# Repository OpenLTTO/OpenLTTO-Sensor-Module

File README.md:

# OpenLTTO
The OpenLTTO Project is an attempt to recreate the Lazer Tag Team Ops protocol, and game system, in a completely open-source solution. Eventually our intent, is to expand on the LTTO system, adding new functionality, and features, while maintaining backwards compatibility with this classic Lazer Tag gear.

> This Project wouldn't be possible without all the hard work of Richie Mickan https://github.com/rmick
> His work on recreating the LTTO Protocol, and the development of the Combobulator app are core to the firmware and capabilities of this project.

> Additionally this is built on top of the excellent product developed and released by Hasbro/Tiger Electronics. And the work done by Tag Ferret to release the technical specs, and unlock much of the magic of the protocol, and the inner workings.

We intend to do this via a collection of open-source hardware components that can act as building blocks, to build anything you might require for a Lazer Tag game (Taggers, Hosting Pods, Zone controllers, utilities, etc). And an opensource firmware to operate it all. 

Shield: [![CC BY-NC-SA 4.0][cc-by-nc-sa-shield]][cc-by-nc-sa]

This work is licensed under a
[Creative Commons Attribution-NonCommercial-ShareAlike 4.0 International License][cc-by-nc-sa].

[![CC BY-NC-SA 4.0][cc-by-nc-sa-image]][cc-by-nc-sa]

[cc-by-nc-sa]: http://creativecommons.org/licenses/by-nc-sa/4.0/
[cc-by-nc-sa-image]: https://licensebuttons.net/l/by-nc-sa/4.0/88x31.png
[cc-by-nc-sa-shield]: https://img.shields.io/badge/License-CC%20BY--NC--SA%204.0-lightgrey.svg

# OpenLTTO Sensor Module
The OpenLTTO Sensor Module is designed to act as either a sensor dome on a Tagger, or a sensor dome on a "Hosting Station" (such as for use with Combobulator), or within a utility component (Zones, Grenades, or any other component you can think of that needs to use 360 degree IR).

It is designed to be paired with a 50mm clear dome, and encased in a 3D Printed "Sensor Module" chassis which can then be embedded in other projects such as Taggers etc.

The module includes 5 Pin IR IN and IR OUT ports, and 4x pairs of IR Transmitter and IR Receiver. The transmitters are more wide angle (TSAL6400) compared to the barrel module, and with this arrangement should provide effective 360 degree coverage. The circuit includes an optimized 1A LED Driver for each IR LED, ensuring full current output per LED. The Module supports both outdoor (high power, 1A), and indoor (low power) modes, controlled from the motherboard. And includes a 2x power ballasts (capacitor, and inrush arrester pair) to prevent ripples, and ensure smooth operation.

## OpenLTTO Sensor Module Top Side

## OpenLTTO Sensor Module Bottom Side

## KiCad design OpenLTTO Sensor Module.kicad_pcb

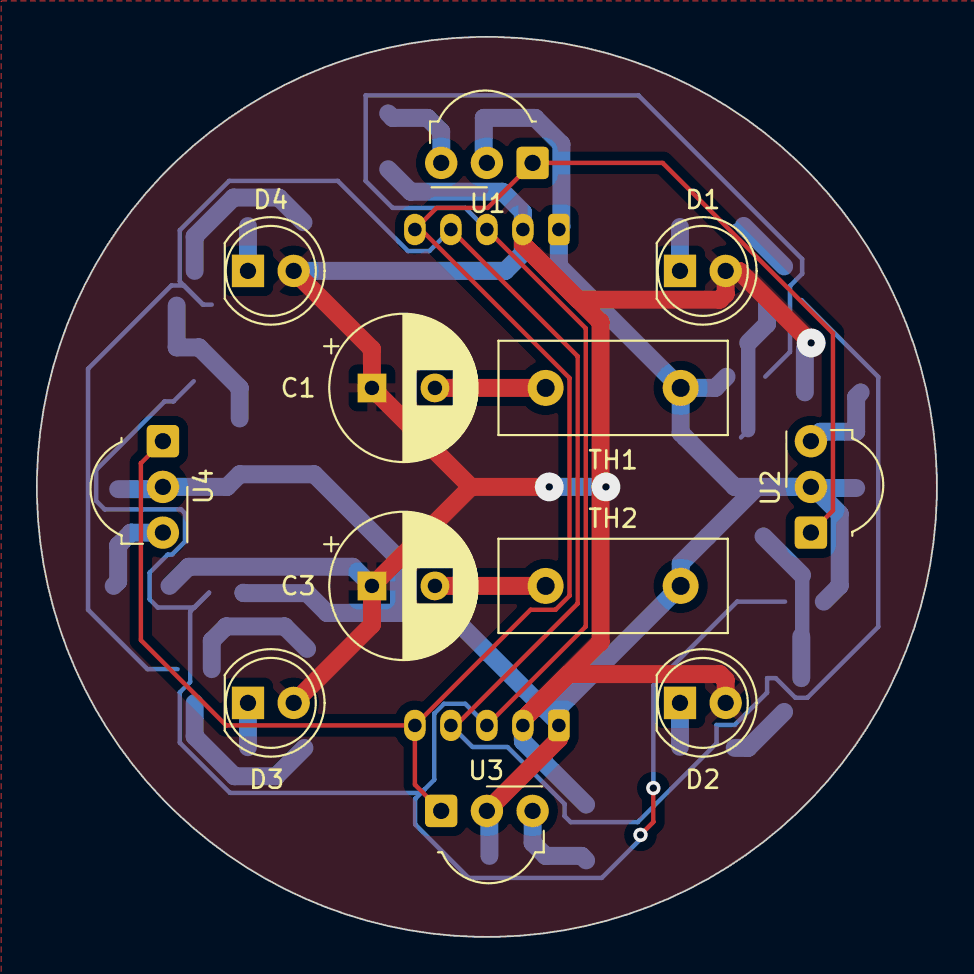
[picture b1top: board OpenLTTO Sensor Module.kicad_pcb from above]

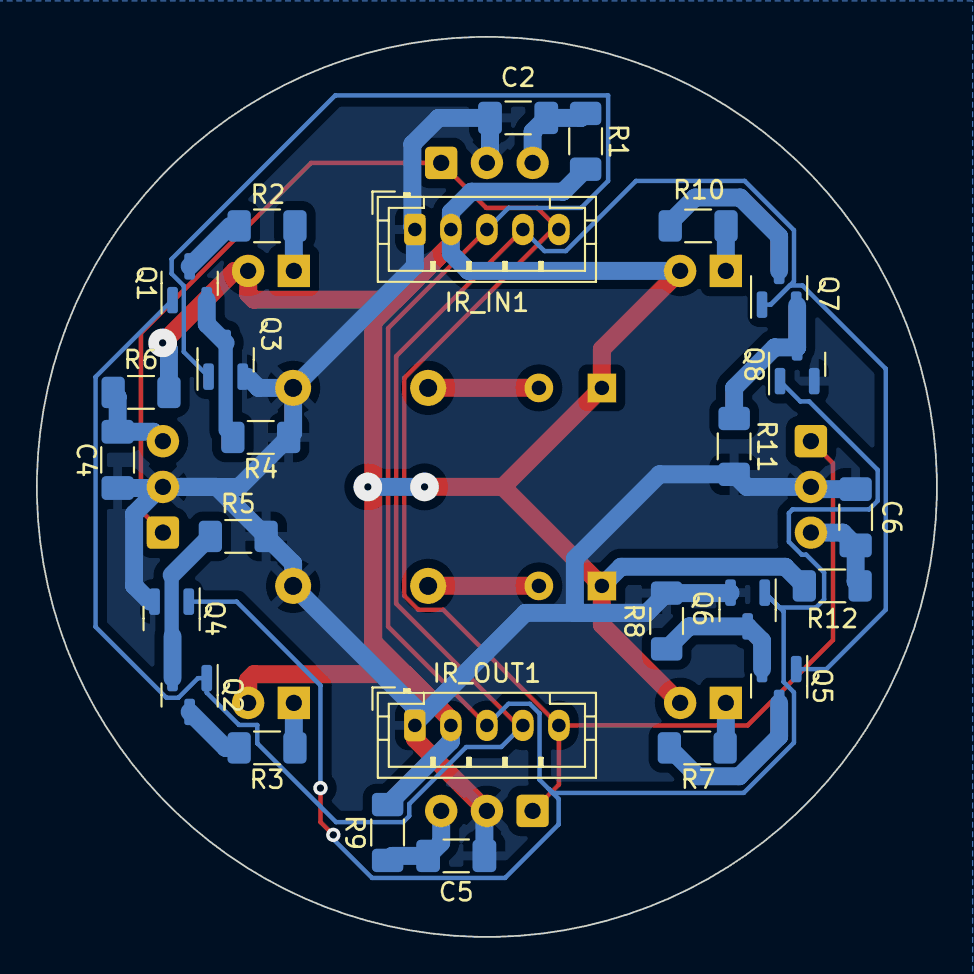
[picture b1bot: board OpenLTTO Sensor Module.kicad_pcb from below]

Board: 2 copper layers, 50.0 x 50.0 mm, 38 parts (26 on the bottom side), 23 nets.

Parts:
C1, C3: 560uf; CP_Radial_D8.0mm_P3.50mm
C2, C4, C5, C6: 0.1uf; C_1206_3216Metric_Pad1.33x1.80mm_HandSolder
D1, D2, D3, D4: TSAL6400; LED_D5.0mm_IRBlack
IR_IN1: JST_PH_B5B-PH-K_1x05_P2.00mm_Vertical
IR_OUT1: JST_PH_B5B-PH-K_1x05_P2.00mm_Vertical
Q1, Q2, Q3, Q4, Q5, Q6, Q7, Q8: IRLML6244; SOT-23
R1, R6, R9, R12: 100; R_1206_3216Metric_Pad1.30x1.75mm_HandSolder
R2, R3, R7, R10: 3.3; R_1206_3216Metric_Pad1.30x1.75mm_HandSolder
R4, R5, R8, R11: 51; R_1206_3216Metric_Pad1.30x1.75mm_HandSolder
TH1, TH2: MF72-050D9; C_Disc_D12.5mm_W5.0mm_P7.50mm
U1, U2, U3, U4: TSOP4138; Vishay_MOLD-3Pin

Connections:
+5V: C1.1, C3.1, D1.2 (A), D2.2 (A), D3.2 (A), D4.2 (A), IR_IN1.2, IR_OUT1.2, R1.2, R6.2, R9.2, R12.2
/IR_MODE: IR_IN1.3, IR_OUT1.3, Q3.1 (G), Q4.1 (G), Q6.1 (G), Q8.1 (G)
/IR_RX: IR_IN1.5, IR_OUT1.5, U1.1 (OUT), U2.1 (OUT), U3.1 (OUT), U4.1 (OUT)
/IR_TX: IR_IN1.4, IR_OUT1.4, Q1.1 (G), Q2.1 (G), Q5.1 (G), Q7.1 (G)
GND: C2.2, C4.2, C5.2, C6.2, IR_IN1.1, IR_OUT1.1, Q3.2 (S), Q4.2 (S), Q6.2 (S), Q8.2 (S), R4.2, R5.2, R8.2, R11.2, TH1.2, TH2.2, U1.2 (GND), U2.2 (GND), U3.2 (GND), U4.2 (GND)
unnamed: C1.2, TH1.1
unnamed: C3.2, TH2.1
unnamed: D1.1 (K), R2.1
unnamed: D2.1 (K), R3.1
unnamed: D3.1 (K), R7.1
unnamed: D4.1 (K), R10.1
unnamed: Q1.3 (D), R2.2
unnamed: Q1.2 (S), Q3.3 (D), R4.1
unnamed: Q2.3 (D), R3.2
unnamed: Q2.2 (S), Q4.3 (D), R5.1
unnamed: Q5.3 (D), R7.2
unnamed: Q5.2 (S), Q6.3 (D), R8.1
unnamed: Q7.3 (D), R10.2
unnamed: Q7.2 (S), Q8.3 (D), R11.1
unnamed: C2.1, R1.1, U1.3 (Vs)
unnamed: C4.1, R6.1, U2.3 (Vs)
unnamed: C5.1, R9.1, U3.3 (Vs)
unnamed: C6.1, R12.1, U4.3 (Vs)

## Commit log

2024-02-01 Updated schematic metadata, added schematic PDF, and PCB Renders
2024-02-02 Added license, and updated readme
